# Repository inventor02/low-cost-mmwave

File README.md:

# low-cost-mmwave

Collaborative Robot Perception with mm-Wave Radar, School of Electronics and Computer Science, University of Southampton

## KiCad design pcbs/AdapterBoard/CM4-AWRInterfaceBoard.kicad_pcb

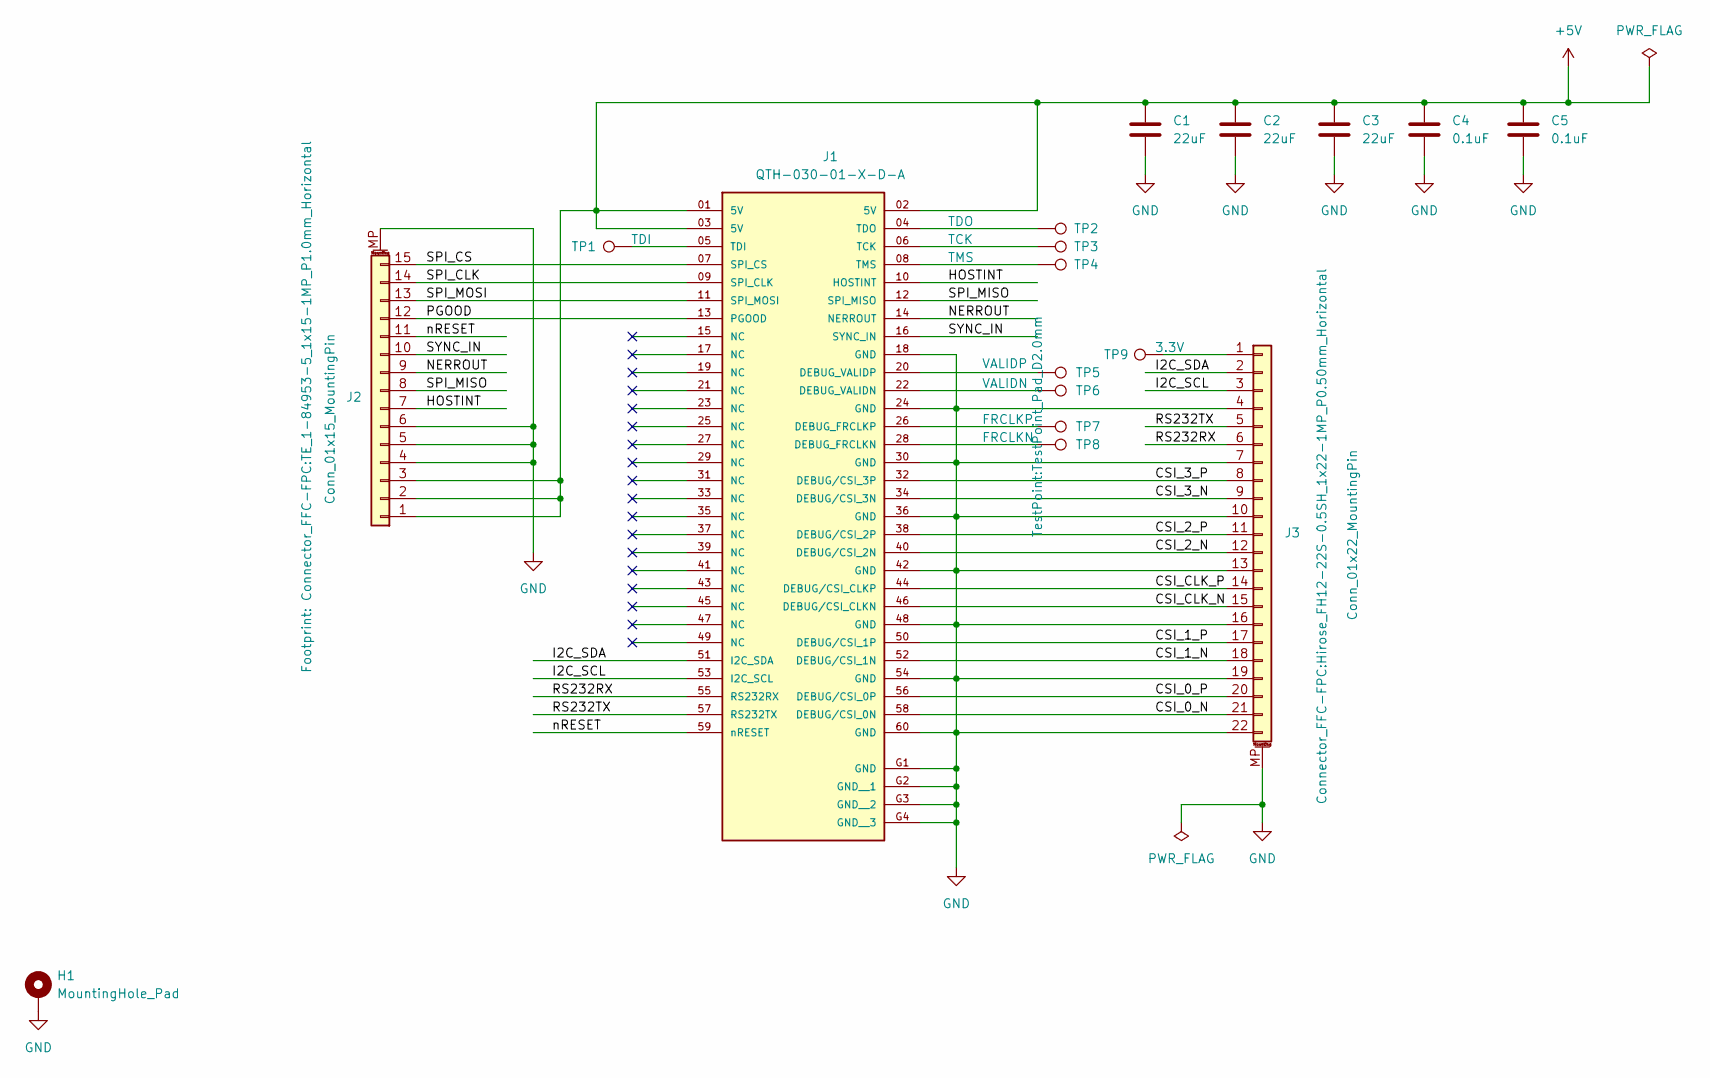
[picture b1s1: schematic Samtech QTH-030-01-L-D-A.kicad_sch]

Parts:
C1, C2, C3: 22uF; C_1206_3216Metric
C4, C5: 0.1uF; C_0805_2012Metric
H1: MountingHole_Pad; MountingHole_4.3mm_M4_Pad_Via
J1: QTH-030-01-X-D-A; SAMTEC-QTH-030-01-X-D-A; PARTREV L
J2: Conn_01x15_MountingPin; TE_1-84953-5_1x15-1MP_P1.0mm_Horizontal
J3: Conn_01x22_MountingPin; Hirose_FH12-22S-0.5SH_1x22-1MP_P0.50mm_Horizontal
TP1: TDI; TestPoint_Pad_D2.0mm
TP2: TDO; TestPoint_Pad_D2.0mm
TP3: TCK; TestPoint_Pad_D2.0mm
TP4: TMS; TestPoint_Pad_D2.0mm
TP5: VALIDP; TestPoint_Pad_D2.0mm
TP6: VALIDN; TestPoint_Pad_D2.0mm
TP7: FRCLKP; TestPoint_Pad_D2.0mm
TP8: FRCLKN; TestPoint_Pad_D2.0mm
TP9: 3.3V; TestPoint_Pad_D2.0mm

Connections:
+5V: C1.1, C2.1, C3.1, C4.1, C5.1, J1.01 (5V), J1.02 (5V), J1.03 (5V), J2.1, J2.2, J2.3
/Samtech QTH-030-01-L-D-A/CSI_0_N: J1.58 (DEBUG/CSI_0N), J3.21
/Samtech QTH-030-01-L-D-A/CSI_0_P: J1.56 (DEBUG/CSI_0P), J3.20
/Samtech QTH-030-01-L-D-A/CSI_1_N: J1.52 (DEBUG/CSI_1N), J3.18
/Samtech QTH-030-01-L-D-A/CSI_1_P: J1.50 (DEBUG/CSI_1P), J3.17
/Samtech QTH-030-01-L-D-A/CSI_2_N: J1.40 (DEBUG/CSI_2N), J3.12
/Samtech QTH-030-01-L-D-A/CSI_2_P: J1.38 (DEBUG/CSI_2P), J3.11
/Samtech QTH-030-01-L-D-A/CSI_3_N: J1.34 (DEBUG/CSI_3N), J3.9
/Samtech QTH-030-01-L-D-A/CSI_3_P: J1.32 (DEBUG/CSI_3P), J3.8
/Samtech QTH-030-01-L-D-A/CSI_CLK_N: J1.46 (DEBUG/CSI_CLKN), J3.15
/Samtech QTH-030-01-L-D-A/CSI_CLK_P: J1.44 (DEBUG/CSI_CLKP), J3.14
/Samtech QTH-030-01-L-D-A/HOSTINT: J1.10 (HOSTINT), J2.7
/Samtech QTH-030-01-L-D-A/I2C_SCL: J1.53 (I2C_SCL), J3.3
/Samtech QTH-030-01-L-D-A/I2C_SDA: J1.51 (I2C_SDA), J3.2
/Samtech QTH-030-01-L-D-A/NERROUT: J1.14 (NERROUT), J2.9
/Samtech QTH-030-01-L-D-A/PGOOD: J1.13 (PGOOD), J2.12
/Samtech QTH-030-01-L-D-A/RS232RX: J1.55 (RS232RX), J3.6
/Samtech QTH-030-01-L-D-A/RS232TX: J1.57 (RS232TX), J3.5
/Samtech QTH-030-01-L-D-A/SPI_CLK: J1.09 (SPI_CLK), J2.14
/Samtech QTH-030-01-L-D-A/SPI_CS: J1.07 (SPI_CS), J2.15
/Samtech QTH-030-01-L-D-A/SPI_MISO: J1.12 (SPI_MISO), J2.8
/Samtech QTH-030-01-L-D-A/SPI_MOSI: J1.11 (SPI_MOSI), J2.13
/Samtech QTH-030-01-L-D-A/SYNC_IN: J1.16 (SYNC_IN), J2.10
/Samtech QTH-030-01-L-D-A/nRESET: J1.59 (nRESET), J2.11
GND: C1.2, C2.2, C3.2, C4.2, C5.2, H1.1, J1.18 (GND), J1.24 (GND), J1.30 (GND), J1.36 (GND), J1.42 (GND), J1.48 (GND), J1.54 (GND), J1.60 (GND), J1.G1 (GND), J1.G2 (GND__1), J1.G3 (GND__2), J1.G4 (GND__3), J2.4, J2.5, J2.6, J2.MP (MountPin), J3.4, J3.7, J3.10, J3.13, J3.16, J3.19, J3.22, J3.MP (MountPin)
unnamed: J1.28 (DEBUG_FRCLKN), TP8.1
unnamed: J1.26 (DEBUG_FRCLKP), TP7.1
unnamed: J1.22 (DEBUG_VALIDN), TP6.1
unnamed: J1.20 (DEBUG_VALIDP), TP5.1
unnamed: J1.06 (TCK), TP3.1
unnamed: J1.05 (TDI), TP1.1
unnamed: J1.04 (TDO), TP2.1
unnamed: J1.08 (TMS), TP4.1
unnamed: J3.1, TP9.1

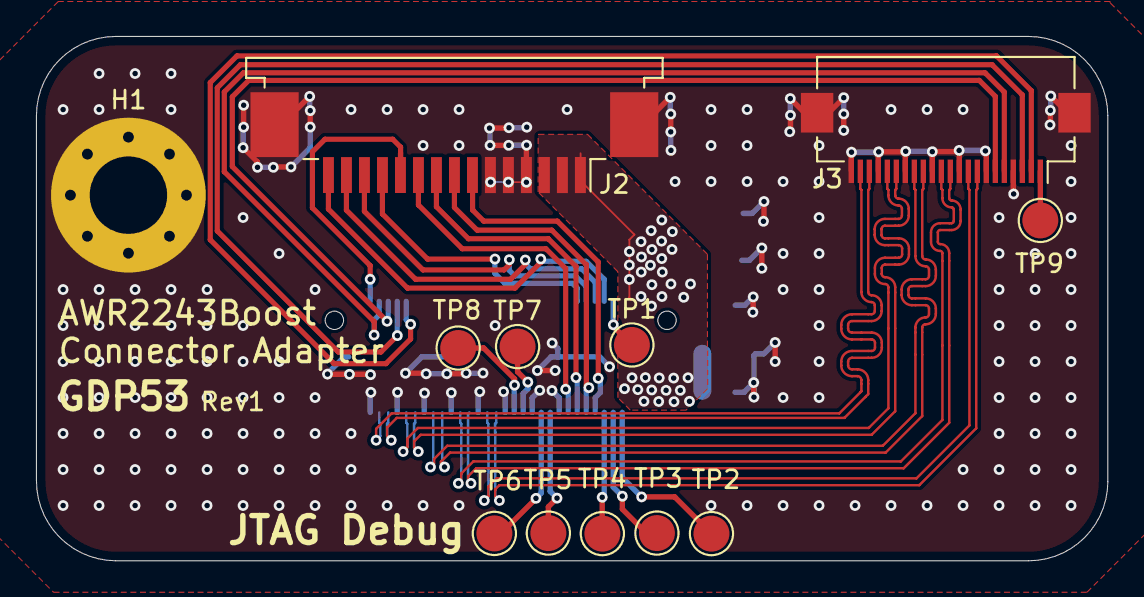
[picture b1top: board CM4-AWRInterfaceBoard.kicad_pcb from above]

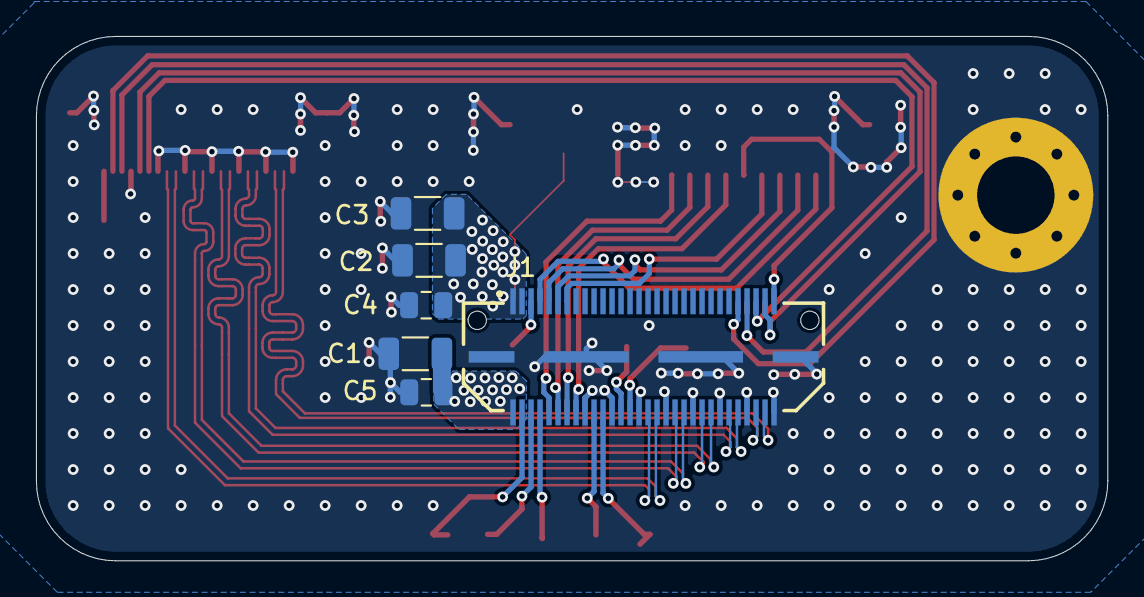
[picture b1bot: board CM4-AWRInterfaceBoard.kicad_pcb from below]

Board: 2 copper layers, 59.5 x 29.1 mm, 18 parts (6 on the bottom side), 34 nets.

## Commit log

2025-01-19 don't add .ds_store
2025-01-20 add risk assessments
2025-01-20 add adapter board
2025-01-20 latest web interface updates
2025-01-20 do not commit archive
